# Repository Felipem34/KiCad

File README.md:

# KiCad
 Here are the projects and libraries

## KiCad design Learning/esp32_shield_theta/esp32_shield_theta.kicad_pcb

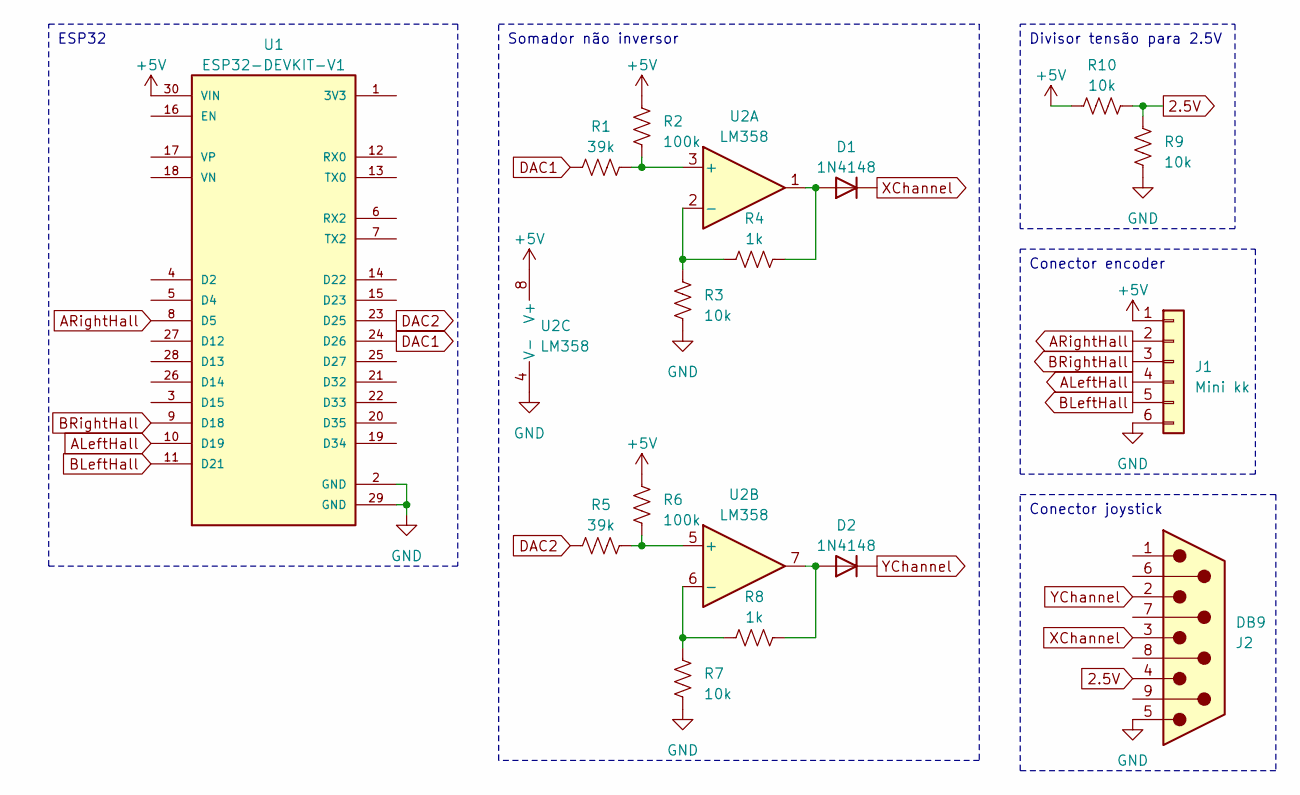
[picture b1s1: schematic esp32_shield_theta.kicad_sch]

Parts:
D1, D2: 1N4148; D_DO-35_SOD27_P7.62mm_Horizontal
J1: Mini kk; Molex_KK-254_AE-6410-06A_1x06_P2.54mm_Vertical
J2: DB9; DSUB-9_Male_Horizontal_P2.77x2.84mm_EdgePinOffset7.70mm_Hou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
R1, R5: 39k; R_Axial_DIN0204_L3.6mm_D1.6mm_P7.62mm_Horizontal
R2, R6: 100k; R_Axial_DIN0204_L3.6mm_D1.6mm_P7.62mm_Horizontal
R3, R7, R9, R10: 10k; R_Axial_DIN0204_L3.6mm_D1.6mm_P7.62mm_Horizontal
R4, R8: 1k; R_Axial_DIN0204_L3.6mm_D1.6mm_P7.62mm_Horizontal
U1: ESP32-DEVKIT-V1; MODULE_ESP32_DEVKIT_V1; PARTREV N/A
U2: LM358; DIP-8_W7.62mm

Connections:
2.5V: J2.4, R9.2, R10.2
+5V: J1.1, R2.1, R6.1, R10.1, U1.30 (VIN), U2.8 (V+)
ALeftHall: J1.4, U1.10 (D19)
ARightHall: J1.2, U1.8 (D5)
BLeftHall: J1.5, U1.11 (D21)
BRightHall: J1.3, U1.9 (D18)
DAC1: R1.1, U1.24 (D26)
DAC2: R5.1, U1.23 (D25)
GND: J1.6, J2.5, R3.1, R7.1, R9.1, U1.2 (GND), U1.29 (GND), U2.4 (V-)
unnamed: D1.2 (A), R4.2, U2.1
unnamed: D2.2 (A), R8.2, U2.7
unnamed: R1.2, R2.2, U2.3 (+)
unnamed: R3.2, R4.1, U2.2 (-)
unnamed: R5.2, R6.2, U2.5 (+)
unnamed: R7.2, R8.1, U2.6 (-)
XChannel: D1.1 (K), J2.3
YChannel: D2.1 (K), J2.2

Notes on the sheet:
Divisor tensão para 2.5V
Conector joystick
Somador não inversor
ESP32
Conector encoder

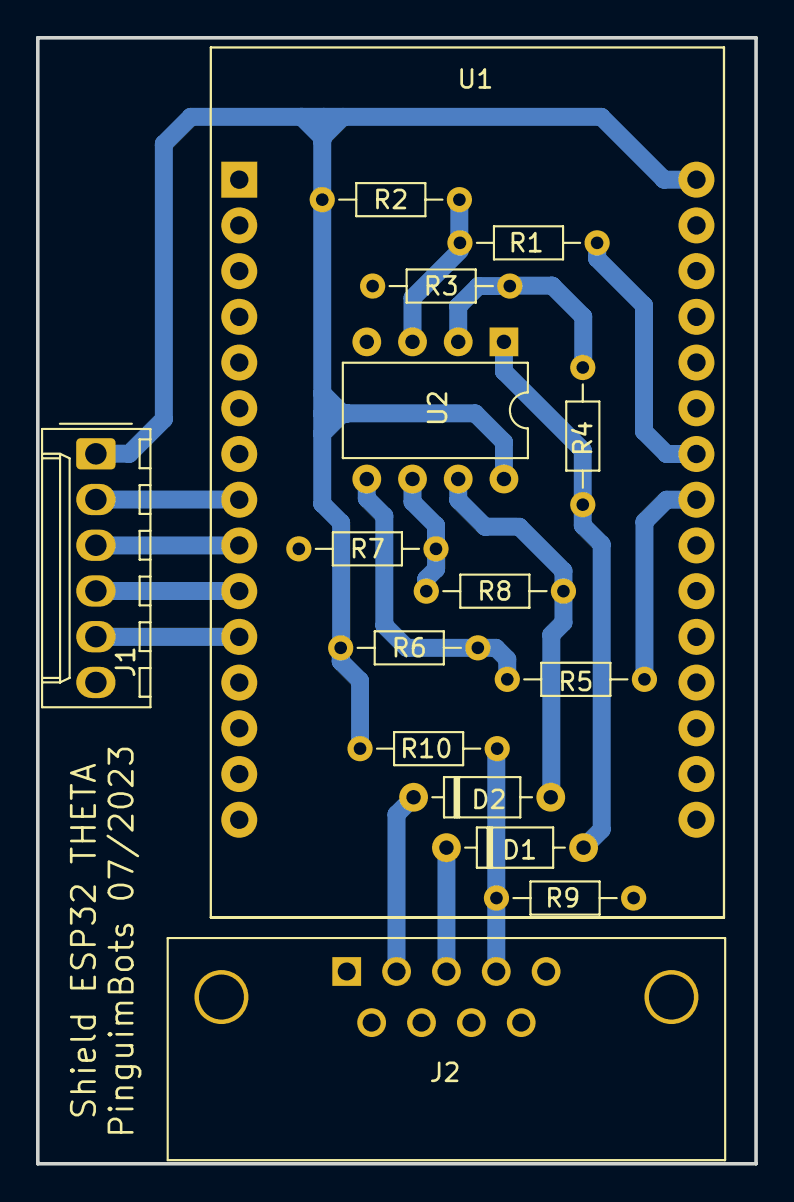
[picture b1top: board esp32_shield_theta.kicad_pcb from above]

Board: 2 copper layers, 39.9 x 62.6 mm, 16 parts (0 on the bottom side), 17 nets.

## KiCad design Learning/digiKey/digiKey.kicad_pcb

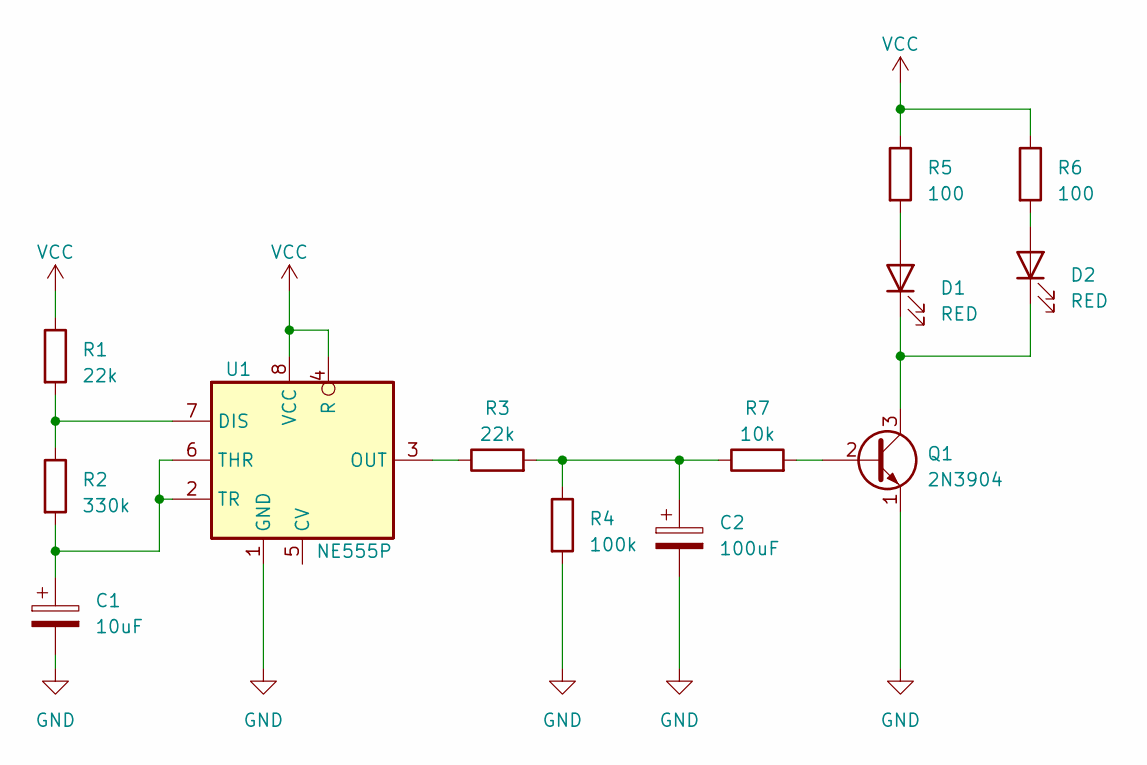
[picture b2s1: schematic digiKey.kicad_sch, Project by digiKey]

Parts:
C1: 10uF; CP_Radial_D5.0mm_P2.00mm
C2: 100uF; CP_Radial_D6.3mm_P2.50mm
D1, D2: RED; LED_D3.0mm
Q1: 2N3904; TO-92_Inline
R1, R3: 22k; R_Axial_DIN0207_L6.3mm_D2.5mm_P7.62mm_Horizontal
R2: 330k; R_Axial_DIN0207_L6.3mm_D2.5mm_P7.62mm_Horizontal
R4: 100k; R_Axial_DIN0207_L6.3mm_D2.5mm_P7.62mm_Horizontal
R5, R6: 100; R_Axial_DIN0207_L6.3mm_D2.5mm_P7.62mm_Horizontal
R7: 10k; R_Axial_DIN0207_L6.3mm_D2.5mm_P7.62mm_Horizontal
U1: NE555P; DIP-8_W7.62mm

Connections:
GND: C1.2, C2.2, Q1.1 (E), R4.2, U1.1 (GND)
unnamed: C2.1, R3.2, R4.1, R7.1
unnamed: D1.2 (A), R5.2
unnamed: D1.1 (K), D2.1 (K), Q1.3 (C)
unnamed: D2.2 (A), R6.2
unnamed: Q1.2 (B), R7.2
unnamed: R1.2, R2.1, U1.7 (DIS)
unnamed: R3.1, U1.3 (OUT)
unnamed: C1.1, R2.2, U1.2 (TR), U1.6 (THR)
VCC: R1.1, R5.1, R6.1, U1.4 (R), U1.8 (VCC)

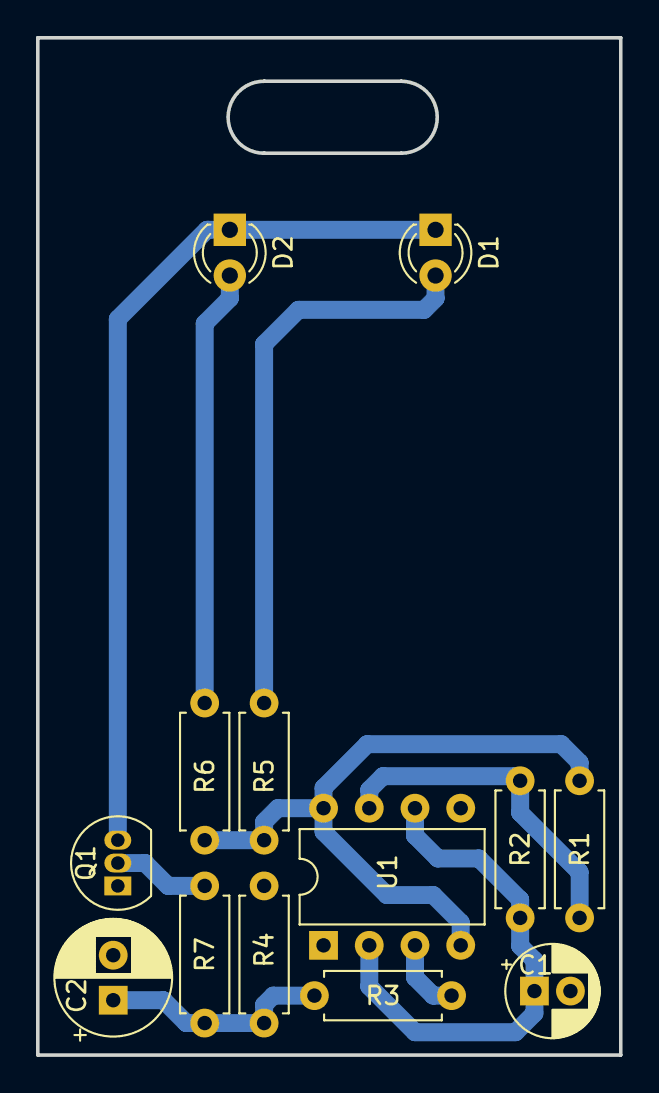
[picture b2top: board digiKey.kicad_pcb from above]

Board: 2 copper layers, 32.4 x 56.5 mm, 13 parts (0 on the bottom side), 10 nets.

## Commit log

2023-07-12 Update on esp32 theta
    change to a up to date version
2023-07-12 remove redundant archive
2023-07-25 Add automatically backup

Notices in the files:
Learning/digiKey/digiKey.kicad_pcb:
creativecommons.org/licenses/by/4.0
License: CC by 4.0
